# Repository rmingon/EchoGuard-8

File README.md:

# GPS Fusion Array with STM32F103

This repository contains the full design files, schematics, and firmware for a **GPS Fusion Array**:
a custom PCB with **8 ATGM336H GNSS modules** and an **STM32F103 MCU** that collects data from all receivers,
performs **real-time fusion**, and outputs the combined solution over **SPI**.

## Support on falconEdge

[FalconEdge repository](https://github.com/rmingon/Falcon-Edge)

---

## Project Overview

| PCB Layout | Schematic     | 3D View |
| ---------- | ------------- | ------- |
| pcb.png    | schematic.png | 3d.png  |

---

## Key Features

- **8× ATGM336H GPS modules** for redundant positioning
- **STM32F103** microcontroller for acquisition and fusion
- **SPI output interface** for fast integration with a master controller
- **Per-module power filtering** and **careful ground plane partitioning** to reduce RF interference
- **Compact, mountable PCB** with 3.3 V power input

---

## Why an Array of GPS Modules?

Traditional single-GPS solutions suffer from multipath, interference, and occasional dropouts.
Using 8 GPS modules in parallel offers:

- **Redundancy:** Even if one receiver loses lock, others keep tracking.
- **Noise Reduction:** Position noise is reduced by averaging multiple solutions.
- **Outlier Rejection:** Bad data can be discarded automatically.
- **Improved Accuracy:** Fusion of multiple measurements yields a more stable, reliable solution.

---

## RF & Interference Mitigation

This PCB design includes several techniques to minimize interference and maintain clean GNSS reception:

- **Dedicated RF Ground Plane:** Each GPS module has local ground pour to reduce mutual coupling.
- **Power Filtering:** Each module’s VCC line is decoupled with LC filters for low-noise operation.
- **Symmetric Layout:** GPS modules are evenly distributed to reduce antenna detuning.
- **Isolated Digital Section:** MCU and SPI routing are kept away from RF traces to reduce emissions.

---

## Data Fusion Algorithm

The STM32F103 runs a lightweight fusion algorithm:

- **NMEA Parsing** from all modules
- **Timestamp Synchronization** for simultaneous position updates
- **Weighted Average & Kalman Filtering** using HDOP as weight
- **Fault Detection:** Rejects outliers and maintains smooth position tracking

---

## Firmware

Features:

- **Complete NMEA Parsing** Supports GGA, RMC, GSA, GSV, VTG, and GLL sentences
- **Interrupt Support** Optional interrupt-driven data reception
- **Comprehensive Data** Position, time, satellites, signal quality, movement data
- **Signal Quality Analysis** SNR monitoring and satellite constellation health

---

## ATGM336H Technical Summary

| Parameter            | Specification                    |
| -------------------- | -------------------------------- |
| Constellations       | GPS, BeiDou, GLONASS, QZSS, SBAS |
| Positioning Accuracy | ~2.5 m CEP                       |
| Cold Start           | < 35 s                           |
| Hot Start            | < 1 s                            |
| Update Rate          | Up to 10 Hz                      |
| Supply Voltage       | 2.8 – 4.3 V                      |
| Interface            | UART (NMEA)                      |
| Tracking Current     | ~26 mA                           |
| Operating Temp       | -40 °C to +85 °C                 |

---

## Hardware Details

- **MCU:** STM32F103C8T6
- **GPS:** 8× ATGM336H modules
- **I/O:** SPI slave output, UARTs for module communication
- **Power:** Single 3.3 V input, on-board filtering
- **Board:** 4-layer PCB, optimized RF layout

---

## Repository Structure

```
/hardware       # KiCad project files, schematics, PCB layout
/firmware       # STM32 source code for GPS fusion and SPI output
/docs           # Project documentation, images, diagrams
```

---

## Getting Started

1. **Assemble the PCB** and mount the GPS modules and STM32.
2. **Flash the firmware** using ST-Link.
3. **Connect SPI** to your master controller (e.g., Raspberry Pi or another STM32).
4. **Power the board** with 3.3 V regulated input.
5. **Start reading fused GPS data** from SPI.

## License

This project is licensed under the **CERN Open Hardware Licence Version 2**. See `LICENSE` file for full terms.

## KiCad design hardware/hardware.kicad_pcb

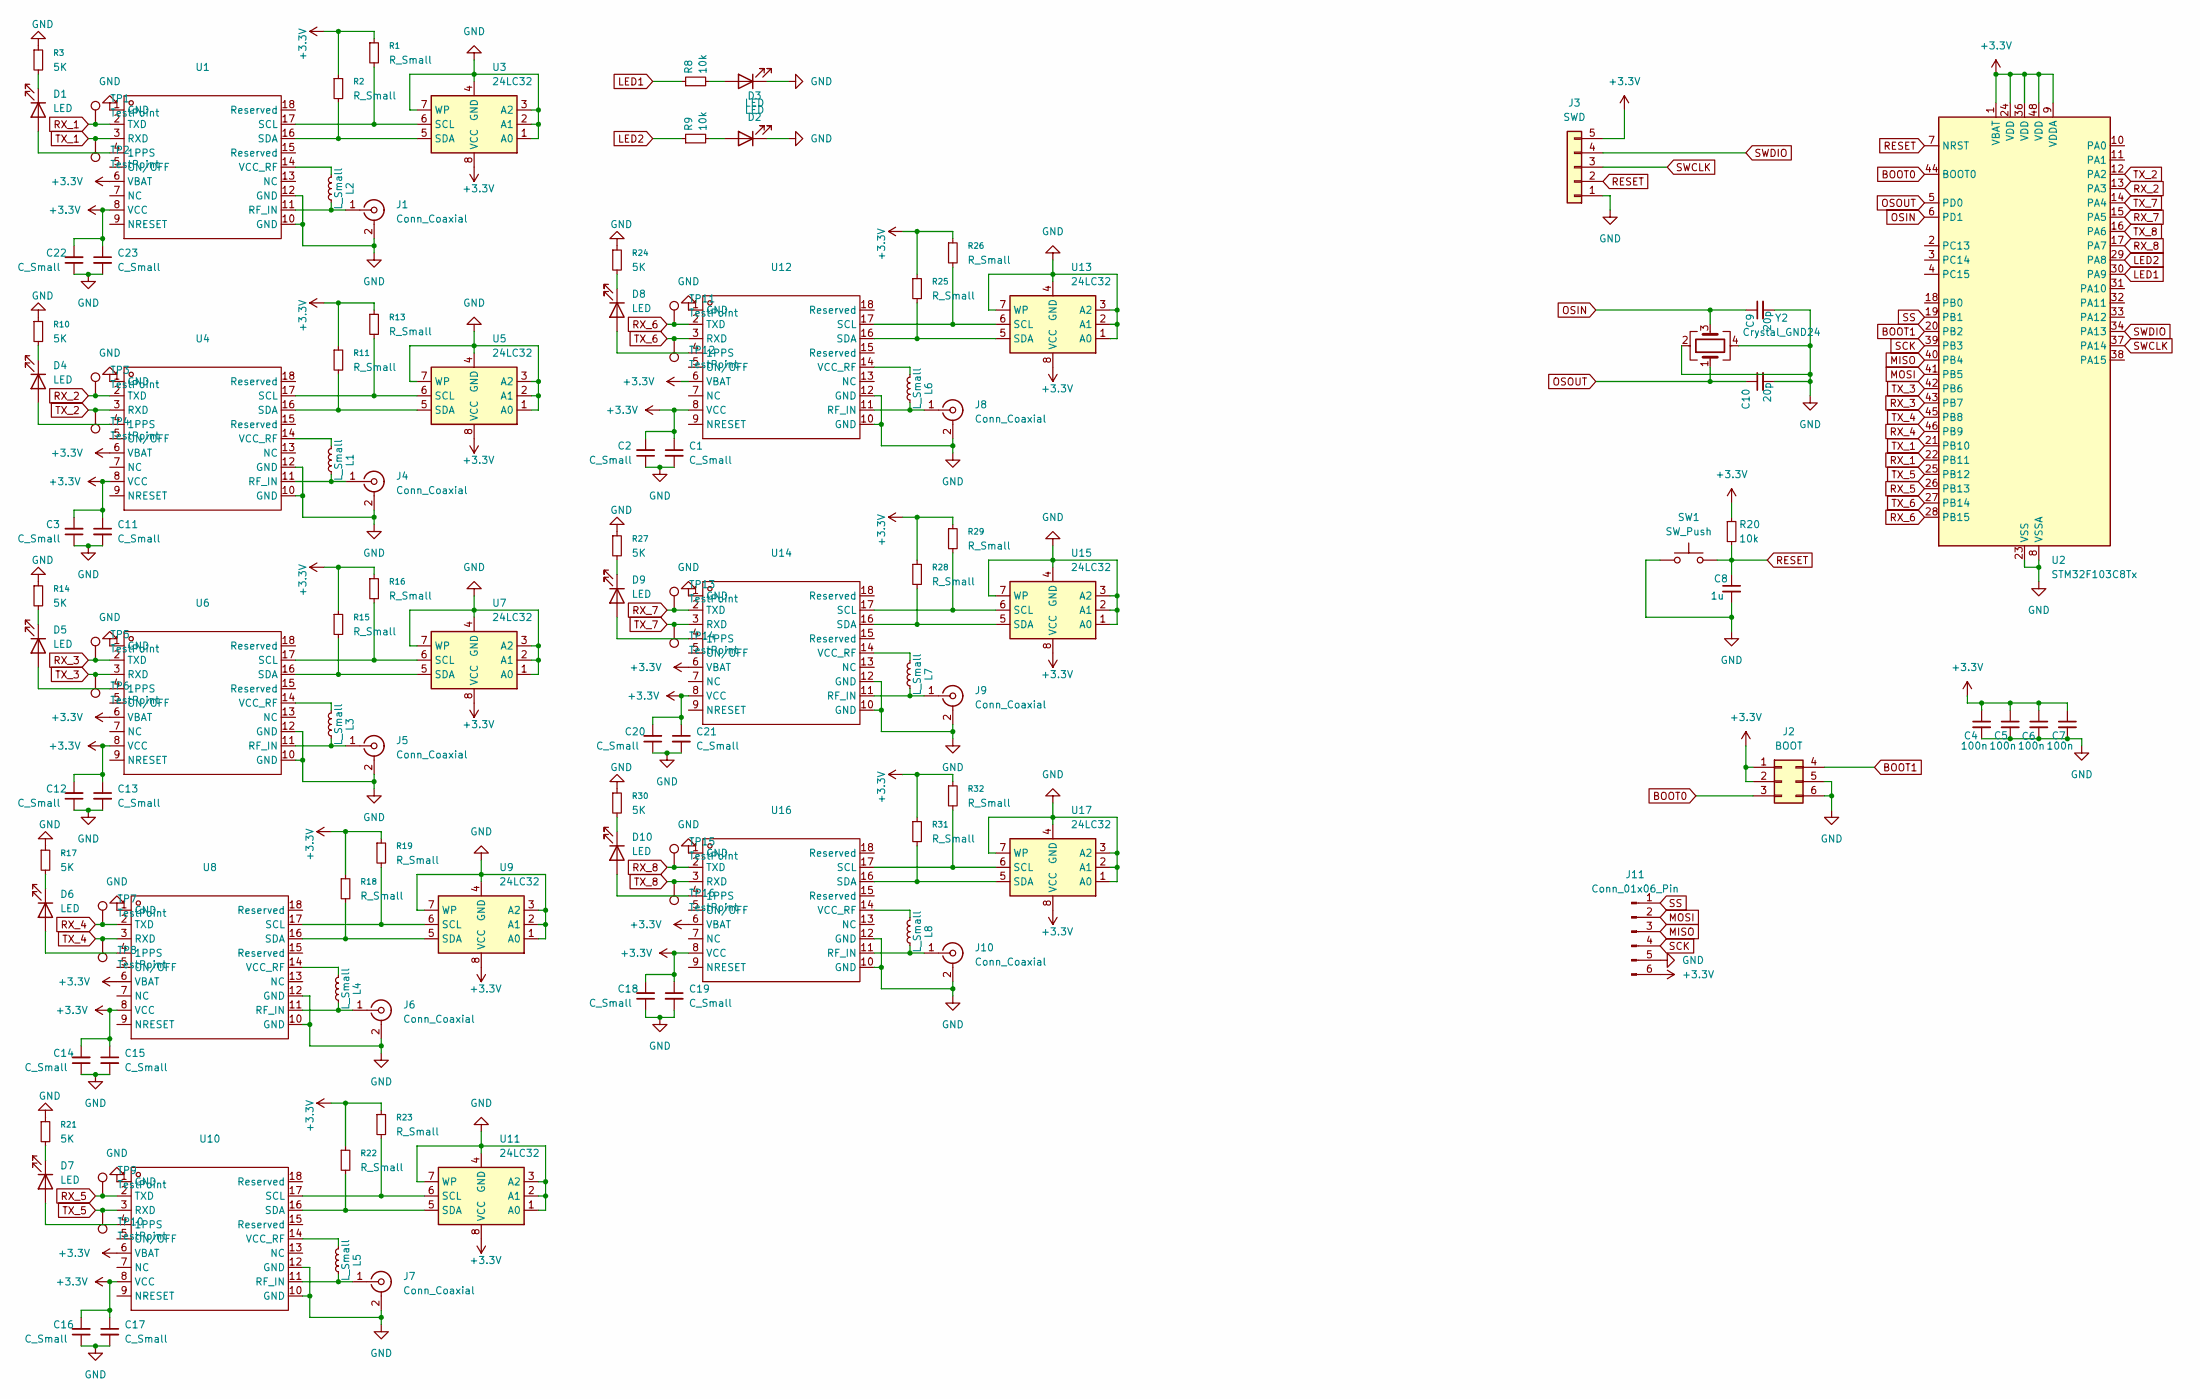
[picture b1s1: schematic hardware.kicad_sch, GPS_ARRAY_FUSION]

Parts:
C1, C11, C13, C15, C17, C19, C21, C23: C_Small; C_0603_1608Metric
C2, C3, C12, C14, C16, C18, C20, C22: C_Small; C_1206_3216Metric
C4, C5, C6, C7: 100n; C_0603_1608Metric
C8: 1u; C_0603_1608Metric
C9, C10: 20p; C_0603_1608Metric
D1, D4, D5, D6, D7, D8, D9, D10: LED; LED_0603_1608Metric
D2, D3: LED; D_0603_1608Metric
J1, J4, J5, J6, J7, J8, J9, J10: Conn_Coaxial; U.FL_Molex_MCRF_73412-0110_Vertical
J2: BOOT; PinHeader_2x03_P2.54mm_Vertical
J3: SWD; PinHeader_1x05_P2.54mm_Vertical
J11: Conn_01x06_Pin; JST_SH_BM06B-SRSS-TB_1x06-1MP_P1.00mm_Vertical
L1, L2, L3, L4, L5, L6, L7, L8: L_Small; L_0603_1608Metric
R1, R2, R11, R13, R15, R16, R18, R19, R22, R23, R25, R26, R28, R29, R31, R32: R_Small; R_0603_1608Metric
R3, R10, R14, R17, R21, R24, R27, R30: 5K; R_0603_1608Metric
R8, R9, R20: 10k; R_0603_1608Metric
SW1: SW_Push; SW_SPST_CK_RS282G05A3
TP1, TP2, TP3, TP4, TP5, TP6, TP7, TP8, TP9, TP10, TP11, TP12, TP13, TP14, TP15, TP16: TestPoint; TestPoint_Pad_D1.5mm
U1, U4, U6, U8, U10, U12, U14, U16: GPSM-SMD_ATGM336H-TR; Manufacturer Part ATGM336H-5N31; LCSC Part Name BDS/GNSS 全星座定位导航模块
U2: STM32F103C8Tx; LQFP-48_7x7mm_P0.5mm
U3, U5, U7, U9, U11, U13, U15, U17: 24LC32; SOIC-8_3.9x4.9mm_P1.27mm
Y2: Crystal_GND24; Crystal_SMD_3225-4Pin_3.2x2.5mm

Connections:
+3.3V: C1.1, C2.2, C3.2, C4.1, C5.1, C6.1, C7.1, C11.1, C12.2, C13.1, C14.2, C15.1, C16.2, C17.1, C18.2, C19.1, C20.2, C21.1, C22.2, C23.1, J2.1, J2.2, J3.5, J11.6, R1.1, R2.1, R11.1, R13.1, R15.1, R16.1, R18.1, R19.1, R20.1, R22.1, R23.1, R25.1, R26.1, R28.1, R29.1, R31.1, R32.1, U1.6 (VBAT), U1.8 (VCC), U2.1 (VBAT), U2.9 (VDDA), U2.24 (VDD), U2.36 (VDD), U2.48 (VDD), U3.8 (VCC), U4.6 (VBAT), U4.8 (VCC), U5.8 (VCC), U6.6 (VBAT), U6.8 (VCC), U7.8 (VCC), U8.6 (VBAT), U8.8 (VCC), U9.8 (VCC), U10.6 (VBAT), U10.8 (VCC), U11.8 (VCC), U12.6 (VBAT), U12.8 (VCC), U13.8 (VCC), U14.6 (VBAT), U14.8 (VCC), U15.8 (VCC), U16.6 (VBAT), U16.8 (VCC), U17.8 (VCC)
BOOT0: J2.3, U2.44 (BOOT0)
BOOT1: J2.4, U2.20 (PB2)
GND: C1.2, C2.1, C3.1, C4.2, C5.2, C6.2, C7.2, C8.2, C9.2, C10.2, C11.2, C12.1, C13.2, C14.1, C15.2, C16.1, C17.2, C18.1, C19.2, C20.1, C21.2, C22.1, C23.2, D2.1 (K), D3.1 (K), J1.2 (Ext), J2.5, J2.6, J3.1, J4.2 (Ext), J5.2 (Ext), J6.2 (Ext), J7.2 (Ext), J8.2 (Ext), J9.2 (Ext), J10.2 (Ext), J11.5, R3.1, R10.1, R14.1, R17.1, R21.1, R24.1, R27.1, R30.1, SW1.1, U1.1 (GND), U1.10 (GND), U1.12 (GND), U2.8 (VSSA), U2.23 (VSS), U2.35 (VSS), U2.47 (VSS), U3.1 (A0), U3.2 (A1), U3.3 (A2), U3.4 (GND), U3.7 (WP), U4.1 (GND), U4.10 (GND), U4.12 (GND), U5.1 (A0), U5.2 (A1), U5.3 (A2), U5.4 (GND), U5.7 (WP), U6.1 (GND), U6.10 (GND), U6.12 (GND), U7.1 (A0), U7.2 (A1), U7.3 (A2), U7.4 (GND), U7.7 (WP), U8.1 (GND), U8.10 (GND), U8.12 (GND), U9.1 (A0), U9.2 (A1), U9.3 (A2), U9.4 (GND), U9.7 (WP), U10.1 (GND), U10.10 (GND), U10.12 (GND), U11.1 (A0), U11.2 (A1), U11.3 (A2), U11.4 (GND), U11.7 (WP), U12.1 (GND), U12.10 (GND), U12.12 (GND), U13.1 (A0), U13.2 (A1), U13.3 (A2), U13.4 (GND), U13.7 (WP), U14.1 (GND), U14.10 (GND), U14.12 (GND), U15.1 (A0), U15.2 (A1), U15.3 (A2), U15.4 (GND), U15.7 (WP), U16.1 (GND), U16.10 (GND), U16.12 (GND), U17.1 (A0), U17.2 (A1), U17.3 (A2), U17.4 (GND), U17.7 (WP), Y2.2, Y2.4
LED1: R8.1, U2.30 (PA9)
LED2: R9.1, U2.29 (PA8)
MISO: J11.3, U2.40 (PB4)
MOSI: J11.2, U2.41 (PB5)
unnamed: D1.2 (A), U1.4 (1PPS)
unnamed: D1.1 (K), R3.2
unnamed: D2.2 (A), R8.2
unnamed: D3.2 (A), R9.2
unnamed: D4.2 (A), U4.4 (1PPS)
unnamed: D4.1 (K), R10.2
unnamed: D5.2 (A), U6.4 (1PPS)
unnamed: D5.1 (K), R14.2
unnamed: D6.2 (A), U8.4 (1PPS)
unnamed: D6.1 (K), R17.2
unnamed: D7.2 (A), U10.4 (1PPS)
unnamed: D7.1 (K), R21.2
unnamed: D8.2 (A), U12.4 (1PPS)
unnamed: D8.1 (K), R24.2
unnamed: D9.2 (A), U14.4 (1PPS)
unnamed: D9.1 (K), R27.2
unnamed: D10.2 (A), U16.4 (1PPS)
unnamed: D10.1 (K), R30.2
unnamed: J1.1 (In), L2.1, U1.11 (RF_IN)
unnamed: J4.1 (In), L1.1, U4.11 (RF_IN)
unnamed: J5.1 (In), L3.1, U6.11 (RF_IN)
unnamed: J6.1 (In), L4.1, U8.11 (RF_IN)
unnamed: J7.1 (In), L5.1, U10.11 (RF_IN)
unnamed: J8.1 (In), L6.1, U12.11 (RF_IN)
unnamed: J9.1 (In), L7.1, U14.11 (RF_IN)
unnamed: J10.1 (In), L8.1, U16.11 (RF_IN)
unnamed: R1.2, U1.17 (SCL), U3.6 (SCL)
unnamed: R2.2, U1.16 (SDA), U3.5 (SDA)
unnamed: L2.2, U1.14 (VCC_RF)
unnamed: R13.2, U4.17 (SCL), U5.6 (SCL)
unnamed: R11.2, U4.16 (SDA), U5.5 (SDA)
unnamed: L1.2, U4.14 (VCC_RF)
unnamed: R16.2, U6.17 (SCL), U7.6 (SCL)
unnamed: R15.2, U6.16 (SDA), U7.5 (SDA)
unnamed: L3.2, U6.14 (VCC_RF)
unnamed: R19.2, U8.17 (SCL), U9.6 (SCL)
unnamed: R18.2, U8.16 (SDA), U9.5 (SDA)
unnamed: L4.2, U8.14 (VCC_RF)
unnamed: R23.2, U10.17 (SCL), U11.6 (SCL)
unnamed: R22.2, U10.16 (SDA), U11.5 (SDA)
unnamed: L5.2, U10.14 (VCC_RF)
unnamed: R26.2, U12.17 (SCL), U13.6 (SCL)
unnamed: R25.2, U12.16 (SDA), U13.5 (SDA)
unnamed: L6.2, U12.14 (VCC_RF)
unnamed: R29.2, U14.17 (SCL), U15.6 (SCL)
unnamed: R28.2, U14.16 (SDA), U15.5 (SDA)
unnamed: L7.2, U14.14 (VCC_RF)
unnamed: R32.2, U16.17 (SCL), U17.6 (SCL)
unnamed: R31.2, U16.16 (SDA), U17.5 (SDA)
unnamed: L8.2, U16.14 (VCC_RF)
OSIN: C9.1, U2.6 (PD1), Y2.3
OSOUT: C10.1, U2.5 (PD0), Y2.1
RESET: C8.1, J3.2, R20.2, SW1.2, U2.7 (NRST)
RX_1: TP1.1 (1_1), U1.2 (TXD), U2.22 (PB11)
RX_2: TP3.1 (1_1), U2.13 (PA3), U4.2 (TXD)
RX_3: TP5.1 (1_1), U2.43 (PB7), U6.2 (TXD)
RX_4: TP7.1 (1_1), U2.46 (PB9), U8.2 (TXD)
RX_5: TP9.1 (1_1), U2.26 (PB13), U10.2 (TXD)
RX_6: TP11.1 (1_1), U2.28 (PB15), U12.2 (TXD)
RX_7: TP13.1 (1_1), U2.15 (PA5), U14.2 (TXD)
RX_8: TP15.1 (1_1), U2.17 (PA7), U16.2 (TXD)
SCK: J11.4, U2.39 (PB3)
SS: J11.1, U2.19 (PB1)
SWCLK: J3.3, U2.37 (PA14)
SWDIO: J3.4, U2.34 (PA13)
TX_1: TP2.1 (1_1), U1.3 (RXD), U2.21 (PB10)
TX_2: TP4.1 (1_1), U2.12 (PA2), U4.3 (RXD)
TX_3: TP6.1 (1_1), U2.42 (PB6), U6.3 (RXD)
TX_4: TP8.1 (1_1), U2.45 (PB8), U8.3 (RXD)
TX_5: TP10.1 (1_1), U2.25 (PB12), U10.3 (RXD)
TX_6: TP12.1 (1_1), U2.27 (PB14), U12.3 (RXD)
TX_7: TP14.1 (1_1), U2.14 (PA4), U14.3 (RXD)
TX_8: TP16.1 (1_1), U2.16 (PA6), U16.3 (RXD)

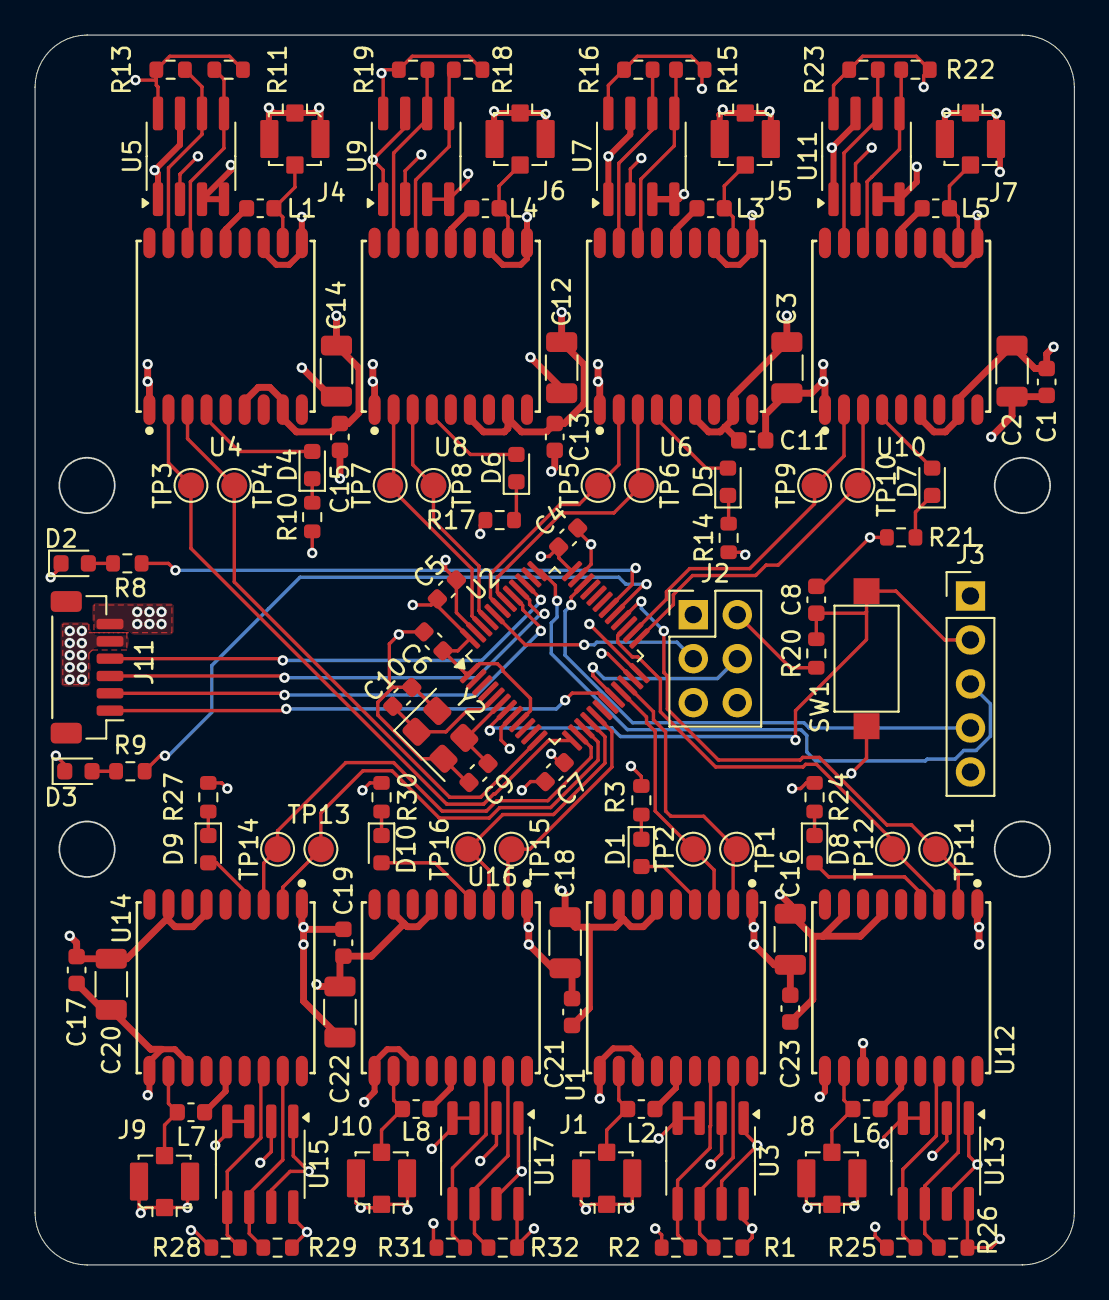
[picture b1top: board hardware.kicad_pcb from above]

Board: 4 copper layers, 60.0 x 71.0 mm, 114 parts (0 on the bottom side), 81 nets.

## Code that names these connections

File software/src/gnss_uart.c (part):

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	__HAL_RCC_GPIOA_CLK_ENABLE();
	__HAL_RCC_GPIOB_CLK_ENABLE();

	/* GNSS #3 uses USART1 remapped to PB6/PB7. */
	__HAL_AFIO_REMAP_USART1_ENABLE();

	for (size_t i = 0; i < GNSS_MODULE_COUNT; i++) {
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
	/*
	 * Note: only GNSS modules #1..#3 are wired to valid STM32F103 hardware USART pin pairs:
	 * - #1: USART3 (PB10/PB11)
	 * - #2: USART2 (PA2/PA3)
	 * - #3: USART1 remap (PB6/PB7)
	 *
	 * Modules #4..#8 require a software UART (or other acquisition method) if you intend to
	 * receive from all 8 modules concurrently.
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
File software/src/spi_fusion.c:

#include "spi_fusion.h"

#include <stddef.h>
#include <string.h>

#include "FreeRTOS.h"
#include "task.h"

#include "gnss_fusion.h"
#include "stm32f1xx_hal.h"

#define SPI_FUSION_MAGIC 0x31464745u /* 'EGF1' little-endian */

static volatile uint8_t tx_buf[SPI_FUSION_PACKET_SIZE];
static volatile uint8_t tx_index;
static volatile uint8_t selected;

static uint16_t crc16_ccitt(const uint8_t *data, size_t len)
{
	uint16_t crc = 0xFFFFu;
	for (size_t i = 0; i < len; i++)
	{
		crc ^= (uint16_t)data[i] << 8;
		for (uint8_t b = 0; b < 8; b++)
		{
			if ((crc & 0x8000u) != 0)
			{
				crc = (uint16_t)((crc << 1) ^ 0x1021u);
			}
			else
			{
				crc <<= 1;
			}
		}
	}
	return crc;
}

static void put_u16_le(uint8_t *dst, uint16_t v)
{
	dst[0] = (uint8_t)(v & 0xFFu);
	dst[1] = (uint8_t)((v >> 8) & 0xFFu);
}

static void put_u32_le(uint8_t *dst, uint32_t v)
{
	dst[0] = (uint8_t)(v & 0xFFu);
	dst[1] = (uint8_t)((v >> 8) & 0xFFu);
	dst[2] = (uint8_t)((v >> 16) & 0xFFu);
	dst[3] = (uint8_t)((v >> 24) & 0xFFu);
}

static void put_i32_le(uint8_t *dst, int32_t v)
{
	put_u32_le(dst, (uint32_t)v);
}

static void build_packet_from_isr(uint8_t out[SPI_FUSION_PACKET_SIZE])
{
	GnssFusionResult r = {0};
	(void)GnssFusion_GetResultFromISR(&r);

	memset(out, 0, SPI_FUSION_PACKET_SIZE);
	put_u32_le(&out[0], SPI_FUSION_MAGIC);
	put_u32_le(&out[4], r.last_update_tick);
	put_i32_le(&out[8], r.lat_e7);
	put_i32_le(&out[12], r.lon_e7);
	put_i32_le(&out[16], r.alt_cm);
	put_u16_le(&out[20], r.avg_hdop_centi);
	put_u16_le(&out[22], r.max_residual_cm);
	out[24] = (uint8_t)r.status;
	out[25] = r.used_modules;
	out[26] = r.rejected_modules;
	out[27] = r.has_fix ? 1u : 0u;

	uint16_t crc = crc16_ccitt(out, SPI_FUSION_PACKET_SIZE - 2u);
	put_u16_le(&out[SPI_FUSION_PACKET_SIZE - 2u], crc);
}

void SpiFusion_Init(void)
{
	__HAL_RCC_AFIO_CLK_ENABLE();
	__HAL_RCC_GPIOB_CLK_ENABLE();
	__HAL_RCC_SPI1_CLK_ENABLE();

	/* PB3/PB4 are JTAG pins; free them while keeping SWD. */
	__HAL_AFIO_REMAP_SWJ_NOJTAG();
	__HAL_AFIO_REMAP_SPI1_ENABLE();

	/* J11 pinout:
	 * 1=SS(PB1), 2=MOSI(PB5), 3=MISO(PB4), 4=SCK(PB3), 5=GND, 6=+3.3V
	 */
	GPIO_InitTypeDef gpio = {0};

	gpio.Pin = GPIO_PIN_3 | GPIO_PIN_5;
	gpio.Mode = GPIO_MODE_INPUT;
	gpio.Pull = GPIO_NOPULL;
	HAL_GPIO_Init(GPIOB, &gpio);

	gpio.Pin = GPIO_PIN_4;
	gpio.Mode = GPIO_MODE_AF_PP;
	gpio.Pull = GPIO_NOPULL;
	gpio.Speed = GPIO_SPEED_FREQ_HIGH;
	HAL_GPIO_Init(GPIOB, &gpio);

	gpio.Pin = GPIO_PIN_1;
	gpio.Mode = GPIO_MODE_IT_RISING_FALLING;
	gpio.Pull = GPIO_PULLUP;
	HAL_GPIO_Init(GPIOB, &gpio);

	HAL_NVIC_SetPriority(EXTI1_IRQn, 6, 0);
	HAL_NVIC_EnableIRQ(EXTI1_IRQn);
	HAL_NVIC_SetPriority(SPI1_IRQn, 6, 0);
	HAL_NVIC_EnableIRQ(SPI1_IRQn);

	/* Configure SPI1 slave, 8-bit, Mode 0, software NSS forced selected (SSI=0). */
	SPI1->CR1 = 0;
	SPI1->CR2 = 0;
	SPI1->CR1 |= SPI_CR1_SSM; /* NSS managed in software. */
	SPI1->CR1 |= SPI_CR1_SSI; /* internal NSS high => not selected */
	SPI1->CR1 &= ~SPI_CR1_CPOL;
	SPI1->CR1 &= ~SPI_CR1_CPHA;
	SPI1->CR1 &= ~SPI_CR1_LSBFIRST;
	SPI1->CR1 &= ~SPI_CR1_MSTR;
	SPI1->CR1 &= ~SPI_CR1_DFF;

	/* Enable interrupts only while SS is asserted to avoid continuous TXE interrupts. */
	SPI1->CR2 |= SPI_CR2_ERRIE;
	SPI1->CR1 |= SPI_CR1_SPE;

	uint8_t packet[SPI_FUSION_PACKET_SIZE];
	build_packet_from_isr(packet);
	memcpy((void *)tx_buf, packet, sizeof(packet));
	tx_index = 0;
	selected = 0;
}

void SpiFusion_SpiIrqHandler(void)
{
	uint16_t sr = SPI1->SR;

	if ((sr & SPI_SR_RXNE) != 0)
	{
		(void)SPI1->DR;
	}

	if ((sr & SPI_SR_TXE) != 0)
	{
		uint8_t byte = 0x00;
		if (selected != 0 && tx_index < SPI_FUSION_PACKET_SIZE)
		{
			byte = tx_buf[tx_index++];
		}
		SPI1->DR = byte;
	}

	if ((sr & SPI_SR_OVR) != 0)
	{
		(void)SPI1->DR;
		(void)SPI1->SR;
	}
}

void HAL_GPIO_EXTI_Callback(uint16_t gpio_pin)
{
	if (gpio_pin != GPIO_PIN_1)
	{
		return;
	}

	GPIO_PinState ss = HAL_GPIO_ReadPin(GPIOB, GPIO_PIN_1);

	if (ss == GPIO_PIN_RESET)
	{
		selected = 1;

		uint8_t packet[SPI_FUSION_PACKET_SIZE];
		build_packet_from_isr(packet);

		SPI1->CR2 &= ~(SPI_CR2_RXNEIE | SPI_CR2_TXEIE);
		(void)SPI1->DR;
		(void)SPI1->SR;
		SPI1->CR1 &= ~SPI_CR1_SSI; /* internal NSS low => selected */
		tx_index = 0;
		memcpy((void *)tx_buf, packet, sizeof(packet));
		if ((SPI1->SR & SPI_SR_TXE) != 0)
		{
			SPI1->DR = tx_buf[tx_index++];
		}
		SPI1->CR2 |= (SPI_CR2_RXNEIE | SPI_CR2_TXEIE);
	}
	else
	{
		SPI1->CR2 &= ~(SPI_CR2_RXNEIE | SPI_CR2_TXEIE);
		selected = 0;
		tx_index = 0;
		SPI1->CR1 |= SPI_CR1_SSI; /* internal NSS high => not selected */
		(void)SPI1->DR;
		(void)SPI1->SR;
	}
}

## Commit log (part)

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2025-09-27 add first gps footprint
2025-09-27 first wiring GPS with LNA
2025-09-27 place all components on pcb
2025-09-27 add power and comm connector
2025-09-28 full wiring pcb
2025-09-28 add pictures
2025-09-28 add connector step
2025-09-28 add readme
2025-09-28 add support image
2025-09-28 add pictures + licence
2025-12-27 add minimal firmware uart control
2025-12-27 fix led pin
2025-12-27 add light fusion system + debug printing
2025-12-27 add spi slave system
2025-12-28 fix gnss ground module
